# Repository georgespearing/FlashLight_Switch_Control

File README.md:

# FlashLight_Switch_Control
Simple Momentary / Push button Switch Controller for LEDs

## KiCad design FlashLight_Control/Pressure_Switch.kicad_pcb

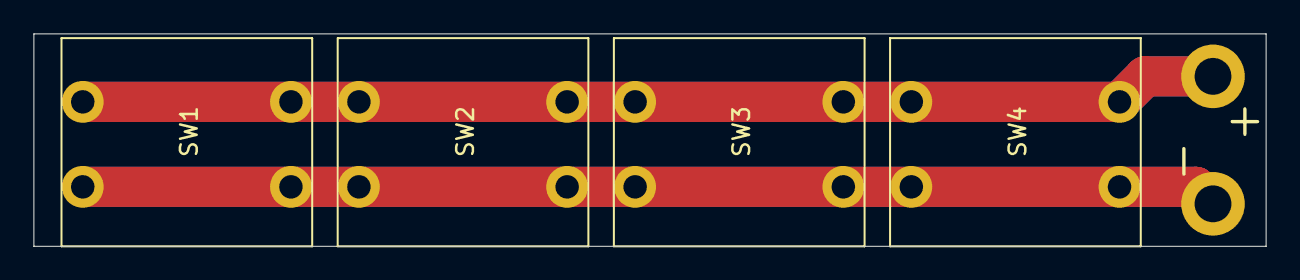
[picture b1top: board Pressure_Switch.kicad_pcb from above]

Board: 2 copper layers, 73.7 x 12.7 mm, 6 parts (0 on the bottom side), 2 nets.

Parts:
H1, H2: MountingHole_Pad; MountingHole_2.2mm_M2_DIN965_Pad
SW1, SW2, SW3, SW4: SW_Push_Dual; button_12mm

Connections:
unnamed: H1.1, SW1.1, SW1.3, SW2.1, SW2.3, SW3.1, SW3.3, SW4.1, SW4.3
unnamed: H2.1, SW1.2, SW1.4, SW2.2, SW2.4, SW3.2, SW3.4, SW4.2, SW4.4

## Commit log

2021-09-30 adding final product
